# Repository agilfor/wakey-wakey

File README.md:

# wakey-wakey

wakey-wakey is a simple alarm clock built on a Seeed Studio XIAO ESP32C3. It runs on C++.

## Features

- TFT Display
- 4 buttons
- Battery or USB-C power
- Deep sleep
- Buzzer
- Alarms (WIP)
- Wi-Fi config (WIP)
- Wi-Fi time sync (WIP)

## CAD

The goal of this model was to make it as symmetrical as possible and as minimalistic as possible. The idea is for it to look simple and be functional as an alarm clock should be.

The current design was made in Onshape. It has screwholes for the PCB, a slot for the TFT display, holes for the buzzer sound, a gap for a USB-C cable, and a top cover with the functions of the buttons engraved.

## PCB

My PCB was made in KiCad. I went a bit more crazy with this than with the CAD, so it took a while. It has 4 keys Charlieplexed to 3 pins, a buzzer, and a TFT display with all pins connected. Additionally, it has been designed with battery functionality in mind. It has a pin header to connect a battery cell to the ESP32C3 VBAT and GND pins (requires some soldering), and uses a nifty voltage divider (with two 220kΩ resistors) connected to an analog pin to allow for battery level measurements. Though these parts fall outside of the standard kit, I have them at home so decided to add them because it's cool and because why not ¯\\\_(ツ)\_/¯

This is my current schematic. It uses charlieplexing to wire the keys (which is how I made space for the battery pin). The downside is it means I need to write more firmware to make it work. Other than that it's not very complicated. There are technically some wires missing (VBAT, GND, and the whole BAT_PWR block) as those require soldering. [More info about the battery trick](https://forum.seeedstudio.com/t/battery-voltage-monitor-and-ad-conversion-for-xiao-esp32c/267535).

This is my PCB. The routing wasn't particularly difficult, but I had fun with it. I mostly ended up making life difficult for myself by trying to make it as small as possible. Also, I spent way too long on the silkscreen designs but no regrets :)

### Wiring/Soldering

Due to the mount style of the XIAO ESP32C3, it is not possible to easily connect the battery pads under the microcontroller to the PCB (technically this is possible using a SMD mount, but it is a pain and much simpler to do some soldering with a DIP mount). The 4 pin male header is the connection of the battery to the microcontroller. It has 4 pins as it requires two pins for VCC and two for GND (connection to the battery cell and connection to the microcontroller). For a more detailed explanation please consult the `battery.md` doc.

## Firmware Overview

The wakey-wakey uses C++ firmware for everything. Currently it supports deep sleep and waking on button press. It should also be able to draw to the TFT display.

Support still needs to be added for all the Wi-Fi functionalities, as well as the alarm, 24H time view toggle, and more. This will be done post-assembly, as some testing needs to be done with the charlieplexed keys before making the script more complicated than it already is.

There will probably be more changes as well to the firmware after all this, but that remains TBD.

## BOM

- 1x Seeed Studio XIAO ESP32C3
- 4x Cherry MX switches
- 4x White blank DSA keycaps
- 1x 2.25in TFT Display
- 1x 3.3V Piezo buzzer
- 1x 2.54mm 8 pin male header
- 8x 20cm female-female jumper wires
- 4x Through-hole 1N4148 Diodes
- 8x M3x5x4 Heatset inserts
- 4x M3x8mm Screws
- 4x M3x16mm Screws

Extra:

- 2x 220kΩ resistors
- 1x 4 pin male header
- LIR2450 battery cell 
- LIR2450 battery holder

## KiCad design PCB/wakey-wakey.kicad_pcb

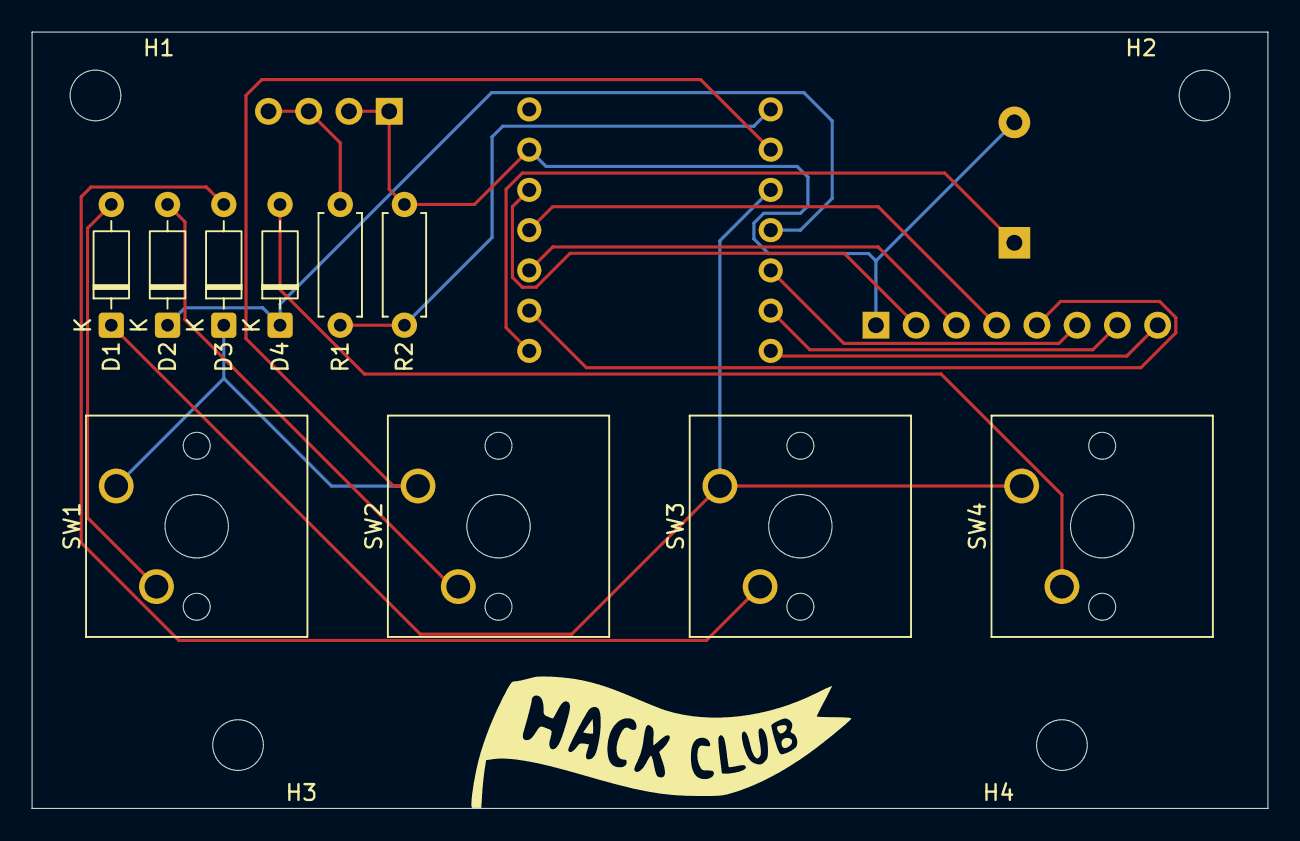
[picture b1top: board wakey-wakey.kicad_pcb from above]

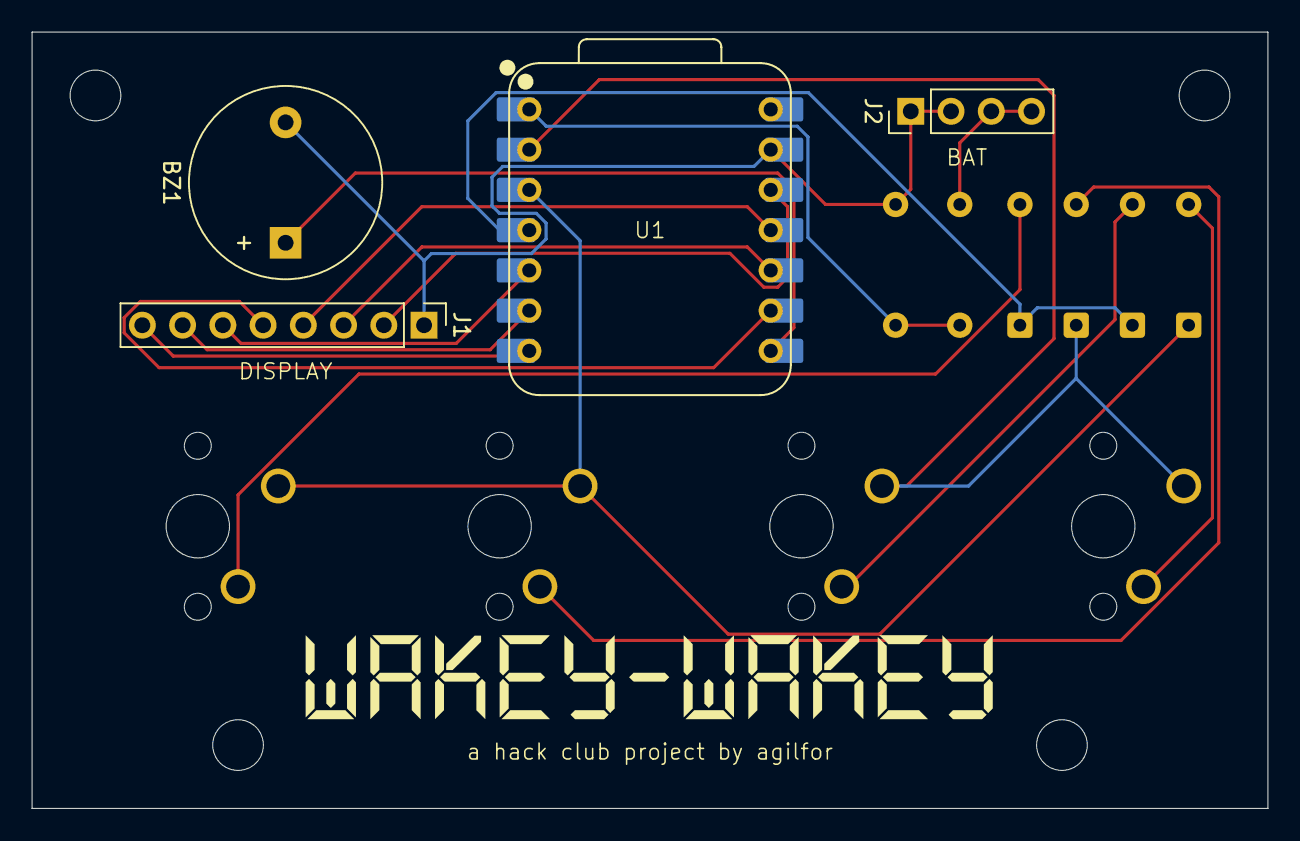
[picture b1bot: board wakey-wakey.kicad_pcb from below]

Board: 2 copper layers, 78.0 x 49.0 mm, 18 parts (4 on the bottom side), 18 nets.

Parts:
BZ1: Buzzer; Buzzer_12x9.5RM7.6
D1, D2, D3, D4: 1N4148; D_DO-35_SOD27_P7.62mm_Horizontal
H1, H2, H3, H4: MountingHole; MountingHole_3.2mm_M3
J1: Display_Conn; PinHeader_1x08_P2.54mm_Vertical
J2: BAT_PWR; PinHeader_1x04_P2.54mm_Vertical
R1, R2: 220k; R_Axial_DIN0207_L6.3mm_D2.5mm_P7.62mm_Horizontal
SW1, SW2, SW3, SW4: SW_Push; SW_Cherry_MX_1.00u_PCB
U1: XIAO-ESP32-C3-SMD; XIAO-ESP32-C3-DIP

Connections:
+3.3V: J1.2, U1.12 (3V3_OUT)
/BAT: R1.1, R2.1, U1.1 (D0)
/BL: J1.8, U1.7 (D6)
/BUZZ: BZ1.1 (+), U1.8 (D7)
/CP1: D3.1 (K), SW1.1, SW2.1, U1.2 (D1)
/CP2: D1.1 (K), SW3.1, SW4.1, U1.3 (D2)
/CP3: D2.1 (K), D4.1 (K), U1.4 (D3)
/CS: J1.7, U1.6 (D5)
/DC: J1.6, U1.5 (D4)
/RST: J1.5, U1.9 (D8)
/SCL: J1.3, U1.10 (D9/BOOT)
/SDA: J1.4, U1.11 (D10)
GND: BZ1.2 (-), J1.1, J2.1, J2.2, R2.2, U1.13 (GND)
unnamed: D1.2 (A), SW1.2
unnamed: D2.2 (A), SW2.2
unnamed: D3.2 (A), SW3.2
unnamed: D4.2 (A), SW4.2
unnamed: J2.3, J2.4, R1.2
